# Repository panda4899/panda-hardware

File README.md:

Panda-Hardware
======

Devices, layouts, schematics, and parts for Team PANDA. 

Some custom parts we made that you may find useful:
* Wurth Electronics Inc 7447462330 Inductor
* ADS1115 Breakout Board
* CAT24C32 32-Kb I2C CMOS Serial EEPROM
* EM7180SFP
* HTU21D Breakout Board
* TSL2561 Breakout Board
* MC74VHC1GT125 Noninverting Buffer / CMOS Logic Level Shifter
* Mini-360 DC/DC
* P82B715 I2C Bus Extender
* Recom R-78E5.0-1.0 switching regulator
* MQ series sensor socket

All of these should work but please check them before you make a board.

MCP23008 from [Adafruit](https://github.com/adafruit/Adafruit-Eagle-Library)

Raspberry Pi B+ GPIO Header 2x20 pin, TSSOP-5, SOT23-5, RJ45-8, LM358, M02, M03, M04, M05, M06, M07, M09, M10, and M12 from [Sparkfun](https://github.com/sparkfun/SparkFun-Eagle-Libraries)

Released under the [Creative Commons ShareAlike 4.0 International](https://creativecommons.org/licenses/by-sa/4.0/) license.

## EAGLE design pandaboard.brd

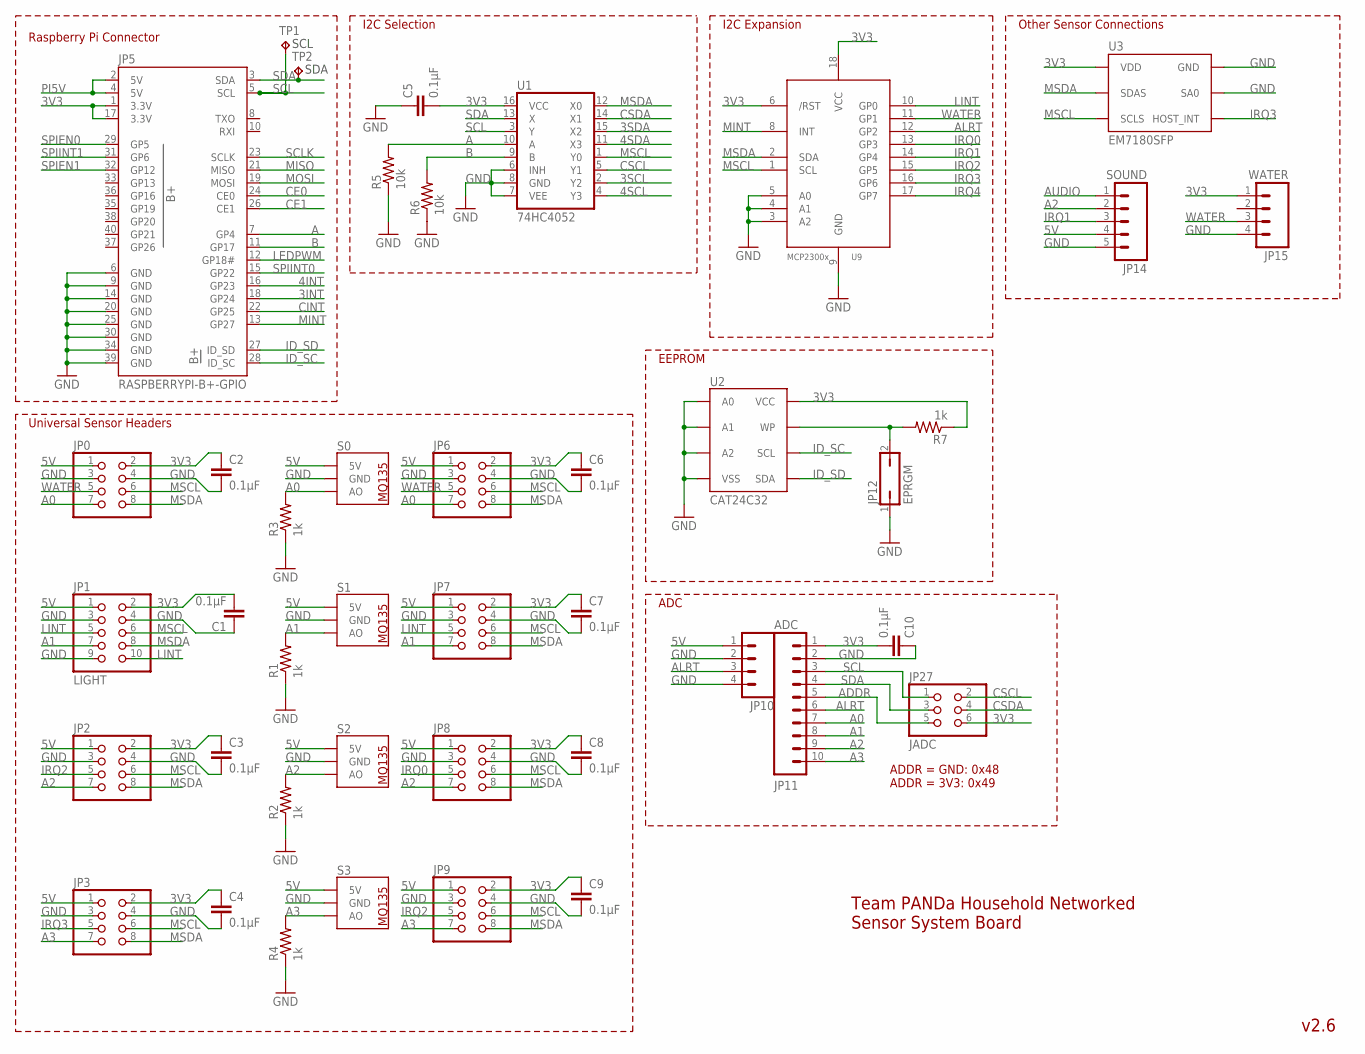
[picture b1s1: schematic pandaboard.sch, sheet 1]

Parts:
C1, C2, C3, C4, C5, C6, C7, C8, C9, C10: 0.1µF; C1206
JP0, JP2, JP3, JP6, JP7, JP8, JP9: PINHD-2X4; 2X04
JP1: LIGHT; 2X05
JP5: RASPBERRYPI-B+-GPIO; 2X20-SHROUDED
JP10: M04PTH; 1X04
JP11: ADC; 1X10
JP12: EPRGM; JP1
JP14: SOUND; 1X05_LOCK
JP15: WATER; 1X04_LOCK
JP27: JADC; 2X03
R1, R2, R3, R4, R7: 1k; R1206
R5, R6: 10k; R1206
S0, S1, S2, S3: VOC
TP1, TP2: TPPAD1-13; P1-13
U1: 74HC4052; DIL16
U2: CAT24C32; DIL08
U3: EM7180SFP
U9: MCP23008/P; DIL18

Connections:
3INT: JP5.18 (GP24); also elsewhere on the board
3SCL: U1.2 (Y2); also elsewhere on the board
3SDA: U1.15 (X2); also elsewhere on the board
3V3: C1.2, C2.1, C3.1, C4.1, C5.2, C6.1, C7.1, C8.1, C9.1, C10.2, JP0.2, JP1.2, JP2.2, JP3.2, JP5.1 (3.3V), JP5.17 (3.3V), JP6.2, JP7.2, JP8.2, JP9.2, JP11.1, JP15.1, JP27.6, R7.1, U1.16 (VCC), U2.8 (VCC), U3.VDD, U9.6 (/RST), U9.18 (VCC); also elsewhere on the board
4INT: JP5.16 (GP23); also elsewhere on the board
4SCL: U1.4 (Y3); also elsewhere on the board
4SDA: U1.11 (X3); also elsewhere on the board
5V: JP0.1, JP1.1, JP2.1, JP3.1, JP6.1, JP7.1, JP8.1, JP9.1, JP10.1, JP14.4, S0.A (5V), S0.A@2 (5V), S0.H (5V), S1.A (5V), S1.A@2 (5V), S1.H (5V), S2.A (5V), S2.A@2 (5V), S2.H (5V), S3.A (5V), S3.A@2 (5V), S3.H (5V); also elsewhere on the board
A: JP5.7 (GP4), R5.2, U1.10 (A)
A0: JP0.7, JP6.7, JP11.7, R3.2, S0.B (AO), S0.B@2 (AO)
A1: JP1.7, JP7.7, JP11.8, R1.2, S1.B (AO), S1.B@2 (AO)
A2: JP2.7, JP8.7, JP11.9, JP14.2, R2.2, S2.B (AO), S2.B@2 (AO)
A3: JP3.7, JP9.7, JP11.10, R4.2, S3.B (AO), S3.B@2 (AO)
ADDR: JP11.5, JP27.5
ALRT: JP10.3, JP11.6, U9.12 (GP2)
AUDIO: JP14.1
B: JP5.11 (GP17), R6.2, U1.9 (B)
CE0: JP5.24 (CE0); also elsewhere on the board
CE1: JP5.26 (CE1); also elsewhere on the board
CINT: JP5.22 (GP25); also elsewhere on the board
CSCL: JP27.2, U1.5 (Y1); also elsewhere on the board
CSDA: JP27.4, U1.14 (X1); also elsewhere on the board
GND: C1.1, C2.2, C3.2, C4.2, C5.1, C6.2, C7.2, C8.2, C9.2, C10.1, JP0.3, JP0.4, JP1.3, JP1.4, JP1.9, JP2.3, JP2.4, JP3.3, JP3.4, JP5.6 (GND), JP5.9 (GND), JP5.14 (GND), JP5.20 (GND), JP5.25 (GND), JP5.30 (GND), JP5.34 (GND), JP5.39 (GND), JP6.3, JP6.4, JP7.3, JP7.4, JP8.3, JP8.4, JP9.3, JP9.4, JP10.2, JP10.4, JP11.2, JP12.1, JP14.5, JP15.4, R1.1, R2.1, R3.1, R4.1, R5.1, R6.1, S0.H@2 (GND), S1.H@2 (GND), S2.H@2 (GND), S3.H@2 (GND), U1.6 (INH), U1.7 (VEE), U1.8 (GND), U2.1 (A0), U2.2 (A1), U2.3 (A2), U2.4 (VSS), U3.GND, U3.SA0, U9.3 (A2), U9.4 (A1), U9.5 (A0), U9.9 (GND); also elsewhere on the board
ID_SC: JP5.28 (ID_SC), U2.6 (SCL)
ID_SD: JP5.27 (ID_SD), U2.5 (SDA)
IRQ0: JP8.5, U9.13 (GP3)
IRQ1: JP14.3, U9.14 (GP4)
IRQ2: JP2.5, JP9.5, U9.15 (GP5)
IRQ3: JP3.5, U3.HOST_INT, U9.16 (GP6)
IRQ4: U9.17 (GP7)
LEDPWM: JP5.12 (GP18#); also elsewhere on the board
LINT: JP1.5, JP1.10, JP7.5, U9.10 (GP0)
MINT: JP5.13 (GP27), U9.8 (INT); also elsewhere on the board
MISO: JP5.21 (MISO); also elsewhere on the board
MOSI: JP5.19 (MOSI); also elsewhere on the board
MSCL: JP0.6, JP1.6, JP2.6, JP3.6, JP6.6, JP7.6, JP8.6, JP9.6, U1.1 (Y0), U3.SCLS, U9.1 (SCL); also elsewhere on the board
MSDA: JP0.8, JP1.8, JP2.8, JP3.8, JP6.8, JP7.8, JP8.8, JP9.8, U1.12 (X0), U3.SDAS, U9.2 (SDA); also elsewhere on the board
unnamed: JP12.2, R7.2, U2.7 (WP)
PI5V: JP5.2 (5V), JP5.4 (5V); also elsewhere on the board
SCL: JP5.5 (SCL), JP11.3, JP27.1, TP1.TP, U1.3 (Y)
SCLK: JP5.23 (SCLK); also elsewhere on the board
SDA: JP5.3 (SDA), JP11.4, JP27.3, TP2.TP, U1.13 (X)
SPIEN0: JP5.29 (GP5); also elsewhere on the board
SPIEN1: JP5.32 (GP12); also elsewhere on the board
SPIINT0: JP5.15 (GP22); also elsewhere on the board
SPIINT1: JP5.31 (GP6); also elsewhere on the board
WATER: JP0.5, JP6.5, JP15.3, U9.11 (GP1)

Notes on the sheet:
v2.6
I2C Selection
Raspberry Pi Connector
Universal Sensor Headers
Other Sensor Connections
I2C Expansion
EEPROM
Team PANDa Household Networked Sensor System Board
ADDR = GND: 0x48 ADDR = 3V3: 0x49
ADC

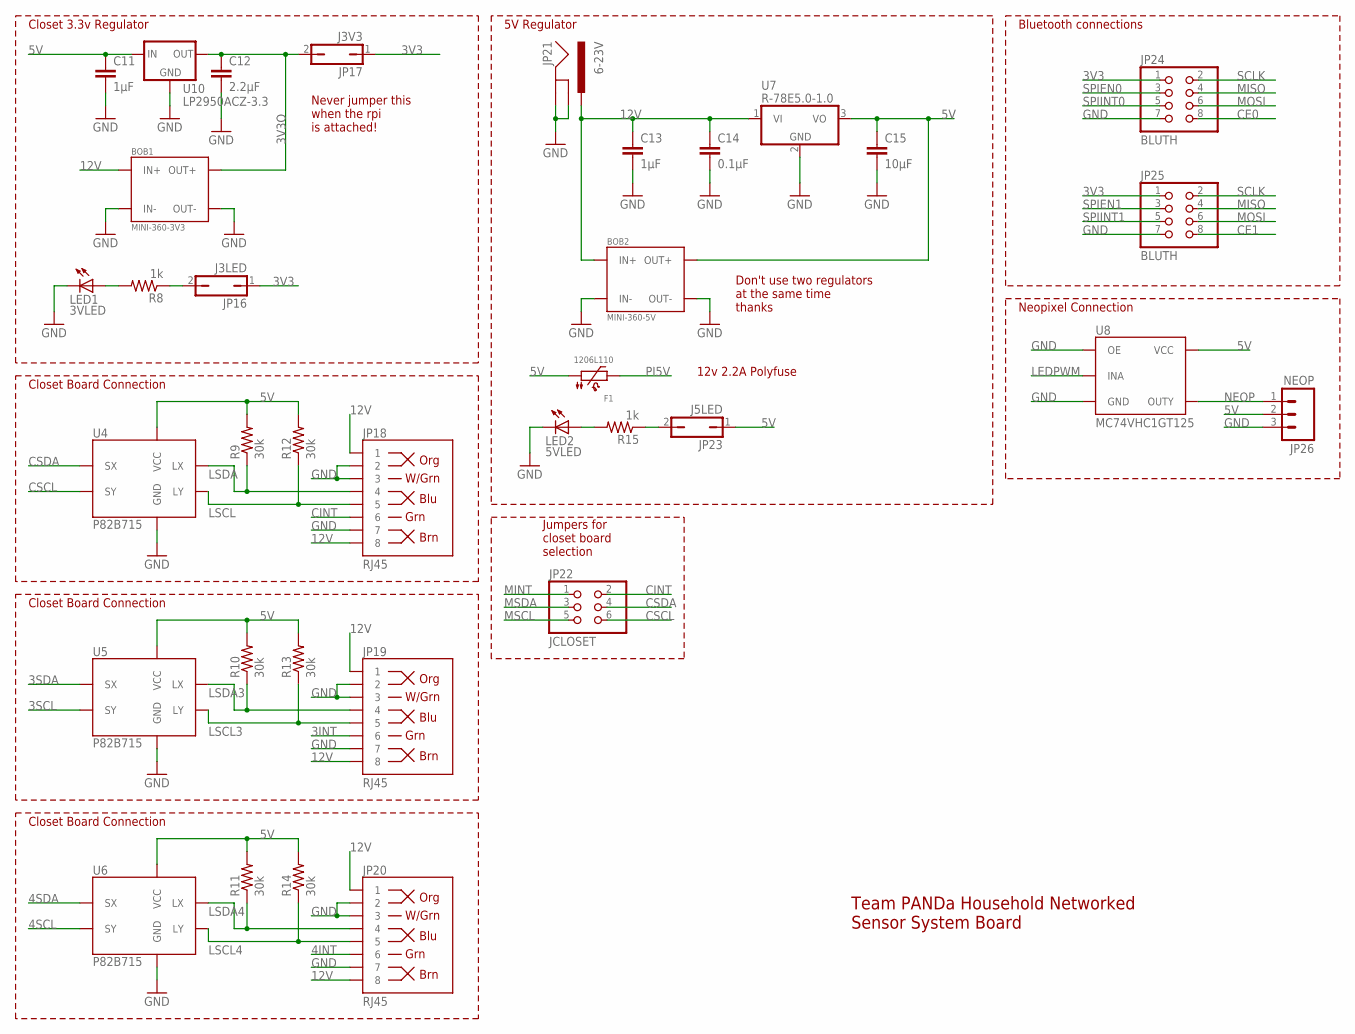
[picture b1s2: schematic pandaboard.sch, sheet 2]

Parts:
BOB1: MINI-360-3V3; MINI-360
BOB2: MINI-360-5V; MINI-360
C11, C13: 1µF; C1206
C12: 2.2µF; C1206
C14: 0.1µF; C1206
C15: 10µF; C1206
F1: 1206L110; 1206
JP16: J3LED; JP1
JP17: J3V3; JP1
JP18, JP19, JP20: RJ45; RJ45-8
JP21: 6-23V; POWER_JACK_PTH_BREAD
JP22: JCLOSET; 2X03
JP23: J5LED; JP1
JP24, JP25: BLUTH; 2X04
JP26: NEOP; 1X03
LED1: 3VLED; LED_1206
LED2: 5VLED; LED_1206
R8, R15: 1k; R1206
R9, R10, R11, R12, R13, R14: 30k; R1206
U4, U5, U6: P82B715; DIL08
U7: R-78E5.0-1.0; R-78E
U8: MC74VHC1GT125; SOT23-5
U10: LP2950ACZ-3.3; TO92

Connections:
3INT: JP19.6; also elsewhere on the board
3SCL: U5.6 (SY); also elsewhere on the board
3SDA: U5.3 (SX); also elsewhere on the board
3V3: JP16.1, JP17.1, JP24.1, JP25.1; also elsewhere on the board
3V3O: BOB1.OUT+, C12.1, JP17.2, U10.1 (OUT)
4INT: JP20.6; also elsewhere on the board
4SCL: U6.6 (SY); also elsewhere on the board
4SDA: U6.3 (SX); also elsewhere on the board
5V: BOB2.OUT+, C11.1, C15.1, F1.1, JP23.1, JP26.2, R9.2, R10.2, R11.2, R12.2, R13.2, R14.2, U4.8 (VCC), U5.8 (VCC), U6.8 (VCC), U7.3 (VO), U8.5 (VCC), U10.3 (IN); also elsewhere on the board
12V: BOB1.IN+, BOB2.IN+, C13.1, C14.1, JP18.1, JP18.8, JP19.1, JP19.8, JP20.1, JP20.8, JP21.PWR, U7.1 (VI)
CE0: JP24.8; also elsewhere on the board
CE1: JP25.8; also elsewhere on the board
CINT: JP18.6, JP22.2; also elsewhere on the board
CSCL: JP22.6, U4.6 (SY); also elsewhere on the board
CSDA: JP22.4, U4.3 (SX); also elsewhere on the board
GND: BOB1.IN-, BOB1.OUT-, BOB2.IN-, BOB2.OUT-, C11.2, C12.2, C13.2, C14.2, C15.2, JP18.2, JP18.3, JP18.7, JP19.2, JP19.3, JP19.7, JP20.2, JP20.3, JP20.7, JP21.GND, JP21.GNDBREAK, JP24.7, JP25.7, JP26.3, LED1.C, LED2.C, U4.4 (GND), U5.4 (GND), U6.4 (GND), U7.2 (GND), U8.1 (OE), U8.3 (GND), U10.2 (GND); also elsewhere on the board
LEDPWM: U8.2 (INA); also elsewhere on the board
LSCL: JP18.5, R12.1, U4.7 (LY)
LSCL3: JP19.5, R13.1, U5.7 (LY)
LSCL4: JP20.5, R14.1, U6.7 (LY)
LSDA: JP18.4, R9.1, U4.2 (LX)
LSDA3: JP19.4, R10.1, U5.2 (LX)
LSDA4: JP20.4, R11.1, U6.2 (LX)
MINT: JP22.1; also elsewhere on the board
MISO: JP24.4, JP25.4; also elsewhere on the board
MOSI: JP24.6, JP25.6; also elsewhere on the board
MSCL: JP22.5; also elsewhere on the board
MSDA: JP22.3; also elsewhere on the board
unnamed: JP23.2, R15.1
unnamed: LED2.A, R15.2
unnamed: LED1.A, R8.2
unnamed: JP16.2, R8.1
NEOP: JP26.1, U8.4 (OUTY)
PI5V: F1.2; also elsewhere on the board
SCLK: JP24.2, JP25.2; also elsewhere on the board
SPIEN0: JP24.3; also elsewhere on the board
SPIEN1: JP25.3; also elsewhere on the board
SPIINT0: JP24.5; also elsewhere on the board
SPIINT1: JP25.5; also elsewhere on the board

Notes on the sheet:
5V Regulator
Closet 3.3v Regulator
Don't use two regulators at the same time thanks
Closet Board Connection
Jumpers for closet board selection
Never jumper this when the rpi is attached!
Bluetooth connections
Neopixel Connection
Team PANDa Household Networked Sensor System Board
12v 2.2A Polyfuse

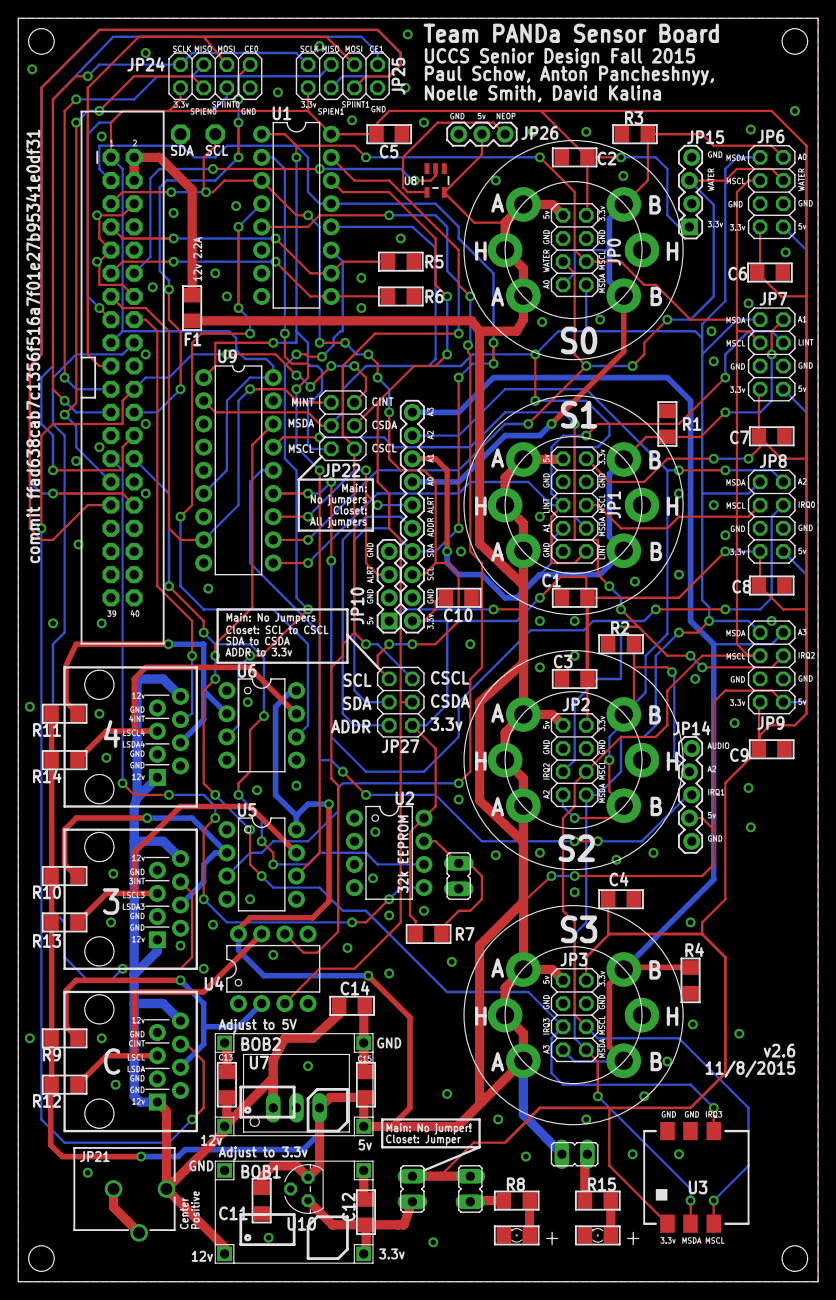
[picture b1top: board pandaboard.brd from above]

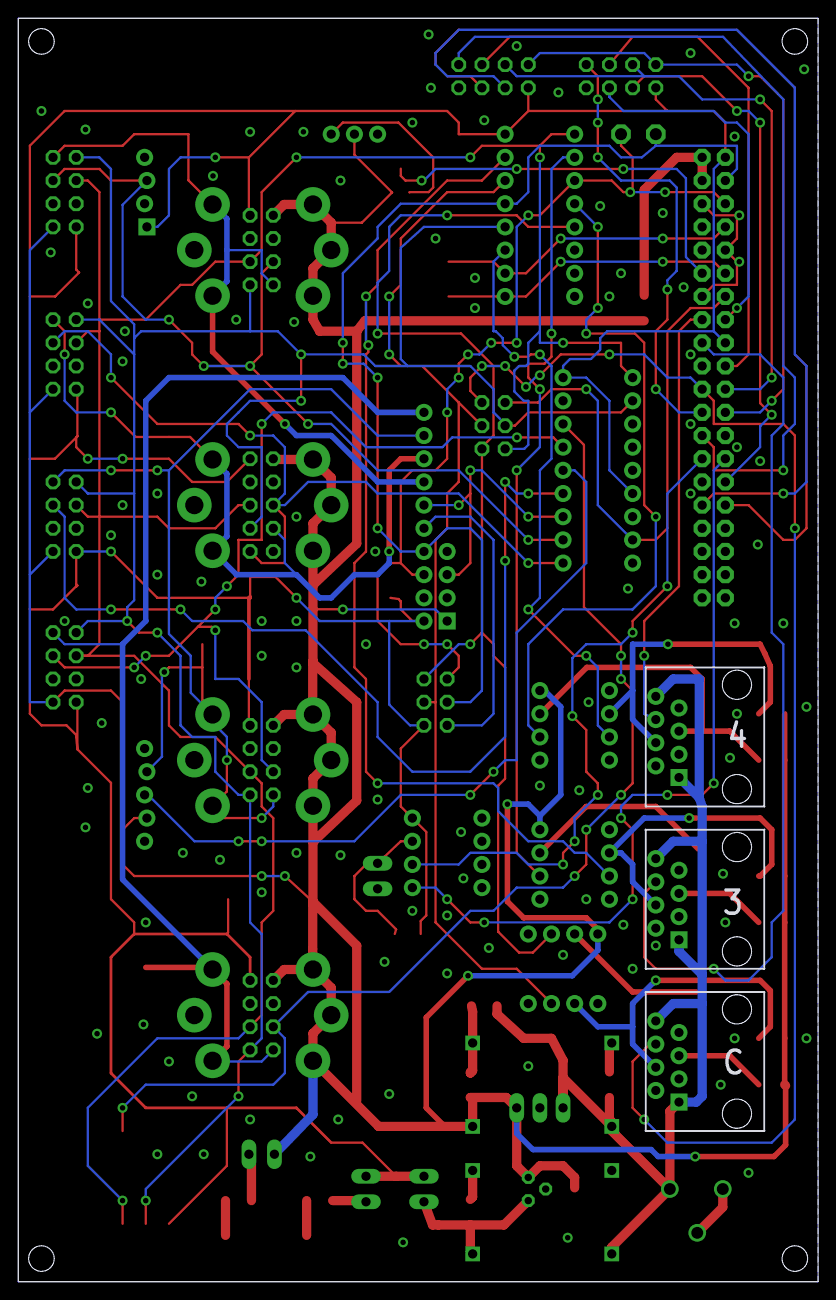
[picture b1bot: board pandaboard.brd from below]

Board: 2 copper layers, 87.6 x 138.4 mm, 78 parts (3 on the bottom side), 58 nets.

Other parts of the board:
U$1: PUPPY

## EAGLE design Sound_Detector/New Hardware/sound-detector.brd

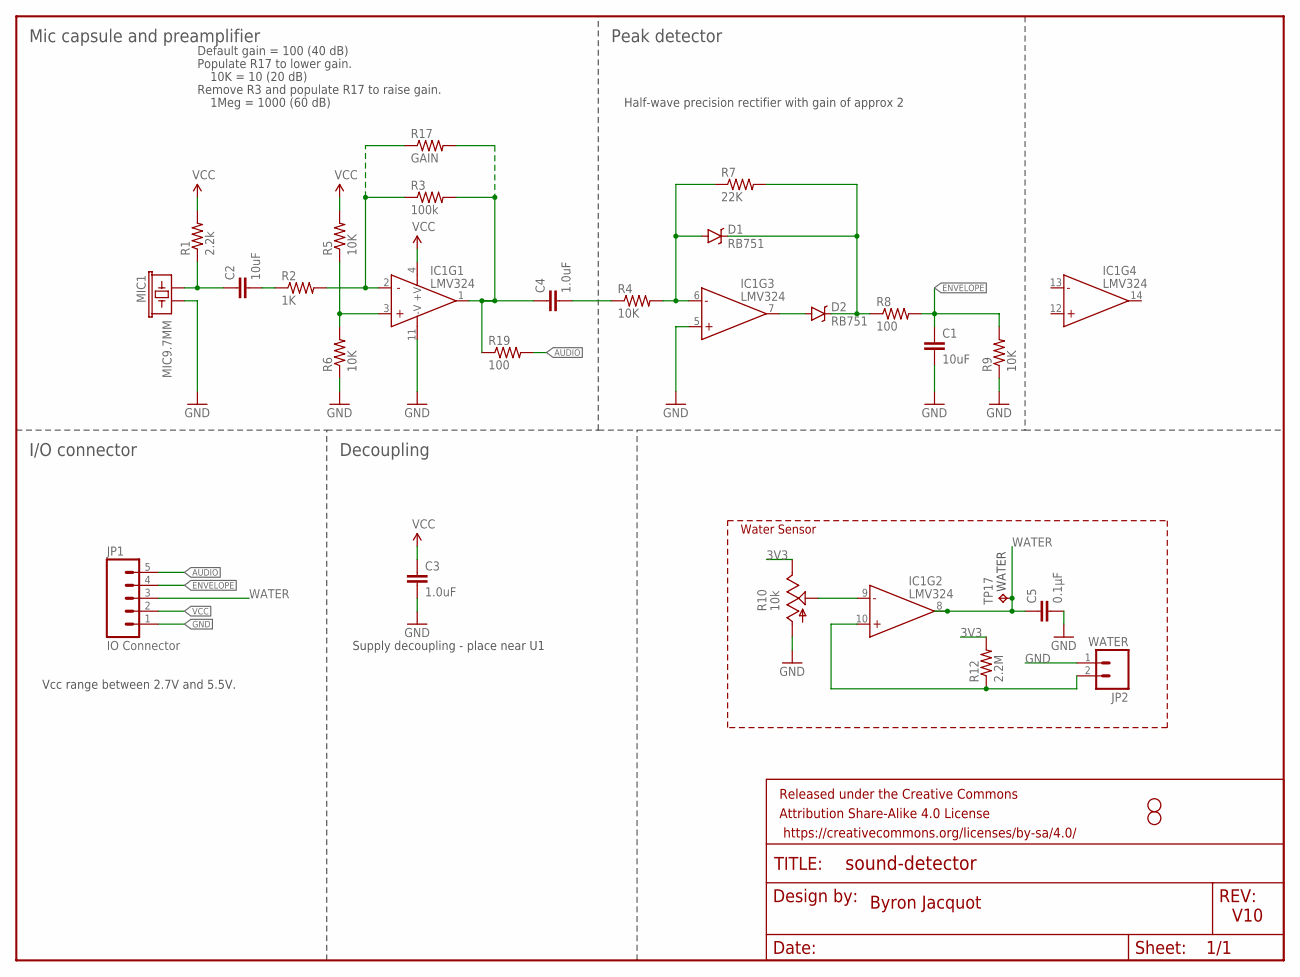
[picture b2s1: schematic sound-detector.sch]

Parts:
C1, C2: 10uF; 1206
C3, C4: 1.0uF; 0603-CAP
C5: 0.1µF; C1206
D1, D2: RB751; SOD-523
FRAME1: FRAME-LETTER; CREATIVE_COMMONS
IC1: LMV324; SO014
JP1: IO Connector; 1X05
JP2: WATER; SCREWTERMINAL-3.5MM-2
MIC1: MIC9.7MM; MIC-9.7MM
R1: 2.2k; 0603-RES@1
R2: 1K; 0603-RES@1
R3: 100k; 0603-RES@1
R4, R5, R6, R9: 10K; 0603-RES@1
R7: 22K; 0603-RES
R8, R19: 100; 0603-RES@1
R10: 10k; B64Y
R12: 2.2M; R1206
R17: GAIN; AXIAL-0.1EZ
STANDOFF1, STANDOFF2: STAND-OFF
TP17: TPPAD1-13; P1-13

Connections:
3V3: R10.E, R12.2
AUDIO: JP1.5, R19.2
ENVELOPE: JP1.4
GND: C1.2, C3.2, C5.2, IC1.5 (+IN), IC1.11 (-V), JP1.1, JP2.1, MIC1.2, R6.1, R9.1, R10.A
N$: C4.1, IC1.1 (OUT), R3.2, R17.P$2 (2), R19.1
unnamed: C2.1, MIC1.1, R1.1
unnamed: IC1.3 (+IN), R5.1, R6.2
unnamed: IC1.2 (-IN), R2.2, R3.1, R17.P$1 (1)
unnamed: C2.2, R2.1
unnamed: C4.2, R4.1
unnamed: D1.A, IC1.6 (-IN), R4.2, R7.1
unnamed: D2.A, IC1.7 (OUT)
unnamed: D1.C, D2.C, R7.2, R8.1
unnamed: C1.1, R8.2, R9.2
unnamed: IC1.9 (-IN), R10.S
unnamed: IC1.10 (+IN), JP2.2, R12.1
VCC: C3.1, IC1.4 (+V), JP1.2, R1.2, R5.2
WATER: C5.1, IC1.8 (OUT), JP1.3, TP17.TP

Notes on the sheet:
Byron Jacquot
V10
Supply decoupling - place near U1
Mic capsule and preamplifier
Peak detector
I/O connector
Decoupling
Default gain = 100 (40 dB)
Half-wave precision rectifier with gain of approx 2
Vcc range between 2.7V and 5.5V.
Populate R17 to lower gain.
10K = 10 (20 dB)
Remove R3 and populate R17 to raise gain.
1Meg = 1000 (60 dB)
Water Sensor

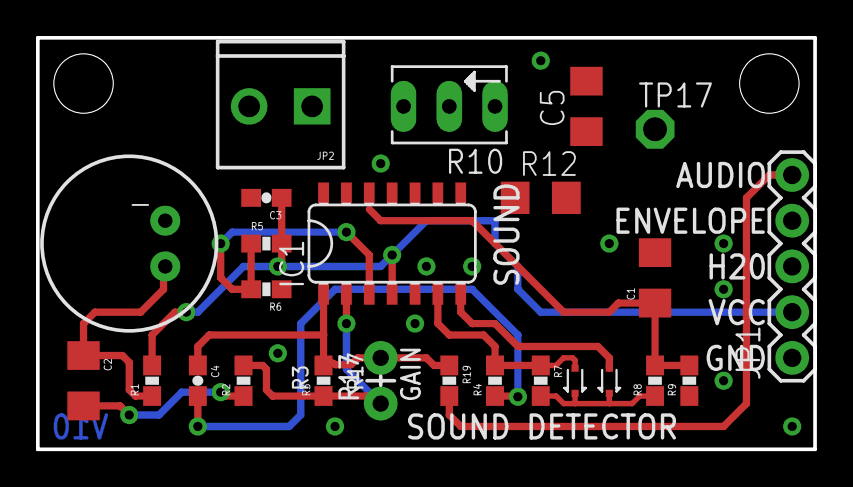
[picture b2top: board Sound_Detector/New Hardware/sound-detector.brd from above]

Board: 2 copper layers, 43.2 x 22.9 mm, 28 parts (0 on the bottom side), 17 nets.

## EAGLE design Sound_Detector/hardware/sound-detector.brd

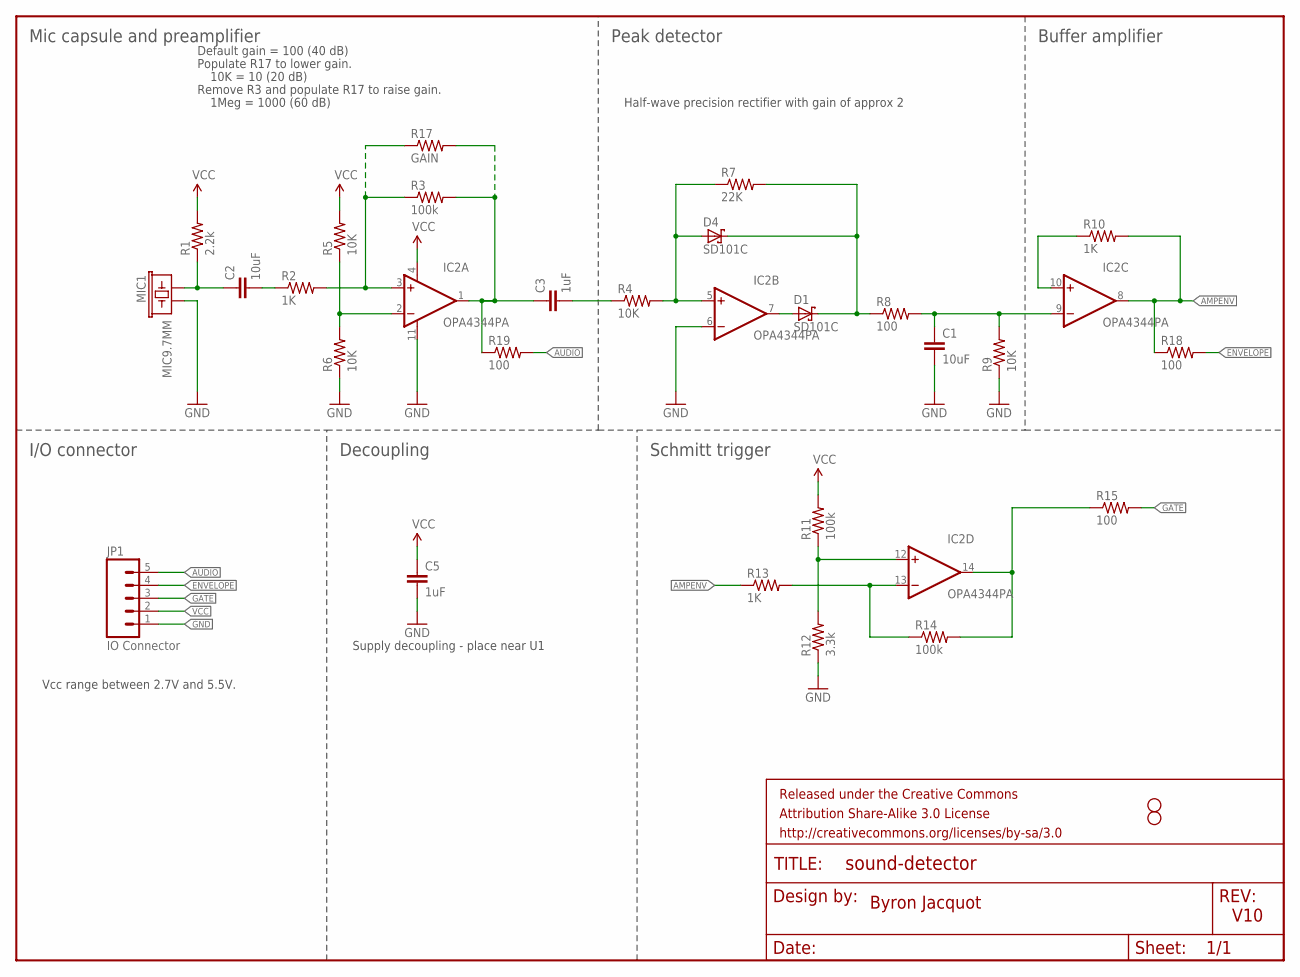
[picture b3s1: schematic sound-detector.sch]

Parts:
C1, C2: 10uF; 1206
C3, C5: 1uF; 1206
D1, D4: SD101C; DO35-7
FRAME1: FRAME-LETTER; CREATIVE_COMMONS
IC2: OPA4344PA; DIL14
JP1: IO Connector; 1X05
MIC1: MIC9.7MM; MIC-9.7MM
R1: 2.2k; R1206
R2, R10, R13: 1K; R1206
R3, R11, R14: 100k; R1206
R4, R5, R6, R9: 10K; R1206
R7: 22K; R1206
R8, R15, R18, R19: 100; R1206
R12: 3.3k; R1206
R17: GAIN; R1206
STANDOFF1, STANDOFF2: STAND-OFF

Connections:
AMPENV: IC2.8 (OUT), R10.2, R13.1, R18.1
AUDIO: JP1.5, R19.2
ENVELOPE: JP1.4, R18.2
GATE: JP1.3, R15.2
GND: C1.2, C5.2, IC2.6 (-IN), IC2.11 (V-), JP1.1, MIC1.2, R6.1, R9.1, R12.1
N$: C3.1, IC2.1 (OUT), R3.2, R17.2, R19.1
unnamed: C2.1, MIC1.1, R1.1
unnamed: IC2.2 (-IN), R5.1, R6.2
unnamed: IC2.3 (+IN), R2.2, R3.1, R17.1
unnamed: C2.2, R2.1
unnamed: C3.2, R4.1
unnamed: D4.A, IC2.5 (+IN), R4.2, R7.1
unnamed: D1.A, IC2.7 (OUT)
unnamed: D1.C, D4.C, R7.2, R8.1
unnamed: C1.1, IC2.9 (-IN), R8.2, R9.2
unnamed: IC2.10 (+IN), R10.1
unnamed: IC2.12 (+IN), R11.1, R12.2
unnamed: IC2.13 (-IN), R13.2, R14.1
unnamed: IC2.14 (OUT), R14.2, R15.1
VCC: C5.1, IC2.4 (V+), JP1.2, R1.2, R5.2, R11.2

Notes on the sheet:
Byron Jacquot
V10
Supply decoupling - place near U1
Mic capsule and preamplifier
Peak detector
Buffer amplifier
I/O connector
Decoupling
Schmitt trigger
Default gain = 100 (40 dB)
Half-wave precision rectifier with gain of approx 2
Vcc range between 2.7V and 5.5V.
Populate R17 to lower gain.
10K = 10 (20 dB)
Remove R3 and populate R17 to raise gain.
1Meg = 1000 (60 dB)

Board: 2 copper layers, 30 parts (0 on the bottom side), 20 nets, no tracks yet.

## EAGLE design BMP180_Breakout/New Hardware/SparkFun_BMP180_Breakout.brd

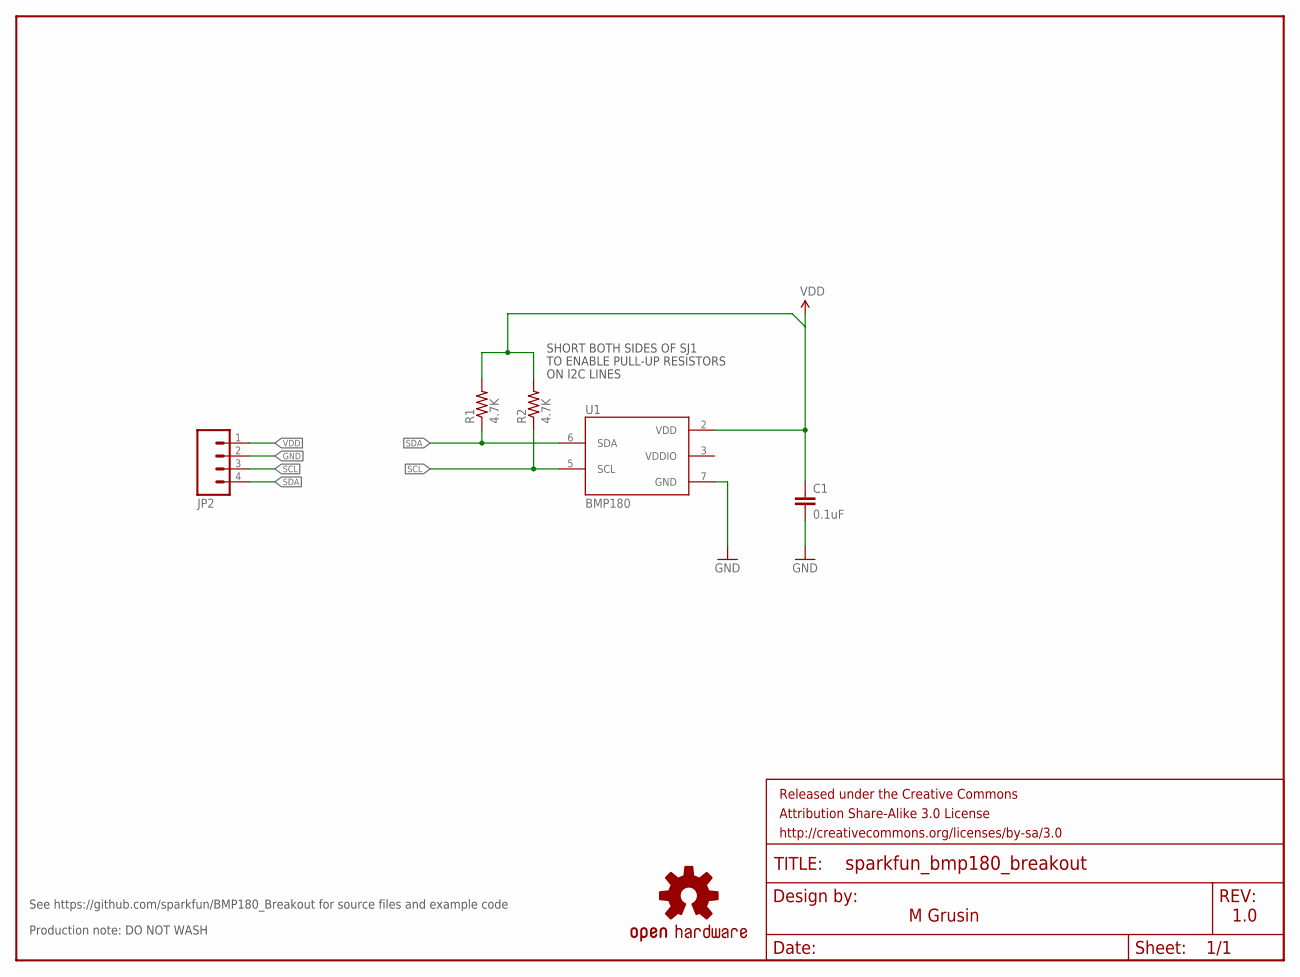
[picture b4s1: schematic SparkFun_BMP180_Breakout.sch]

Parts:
C1: 0.1uF; 0603-CAP
FRAME1: FRAME-LETTER; CREATIVE_COMMONS
JP2: M04PTH; 1X04
LOGO2: OSHW-LOGOS; OSHW-LOGO-S
R1, R2: 4.7K; 0603-RES
U1: BMP180

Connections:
GND: C1.2, JP2.2, U1.7 (GND)
SCL: JP2.3, R2.1, U1.5 (SCL)
SDA: JP2.4, R1.1, U1.6 (SDA)
VDD: C1.1, JP2.1, R1.2, R2.2, U1.2 (VDD)
VDDIO: U1.3 (VDDIO)

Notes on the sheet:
M Grusin
SHORT BOTH SIDES OF SJ1
TO ENABLE PULL-UP RESISTORS
ON I2C LINES
1.0
Production note: DO NOT WASH
See https://github.com/sparkfun/BMP180_Breakout for source files and example code

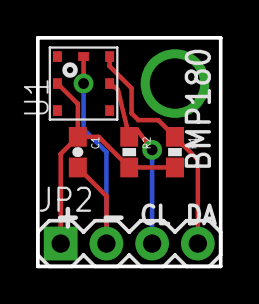
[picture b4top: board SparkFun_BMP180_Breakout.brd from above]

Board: 2 copper layers, 10.2 x 12.7 mm, 7 parts (1 on the bottom side), 4 nets.

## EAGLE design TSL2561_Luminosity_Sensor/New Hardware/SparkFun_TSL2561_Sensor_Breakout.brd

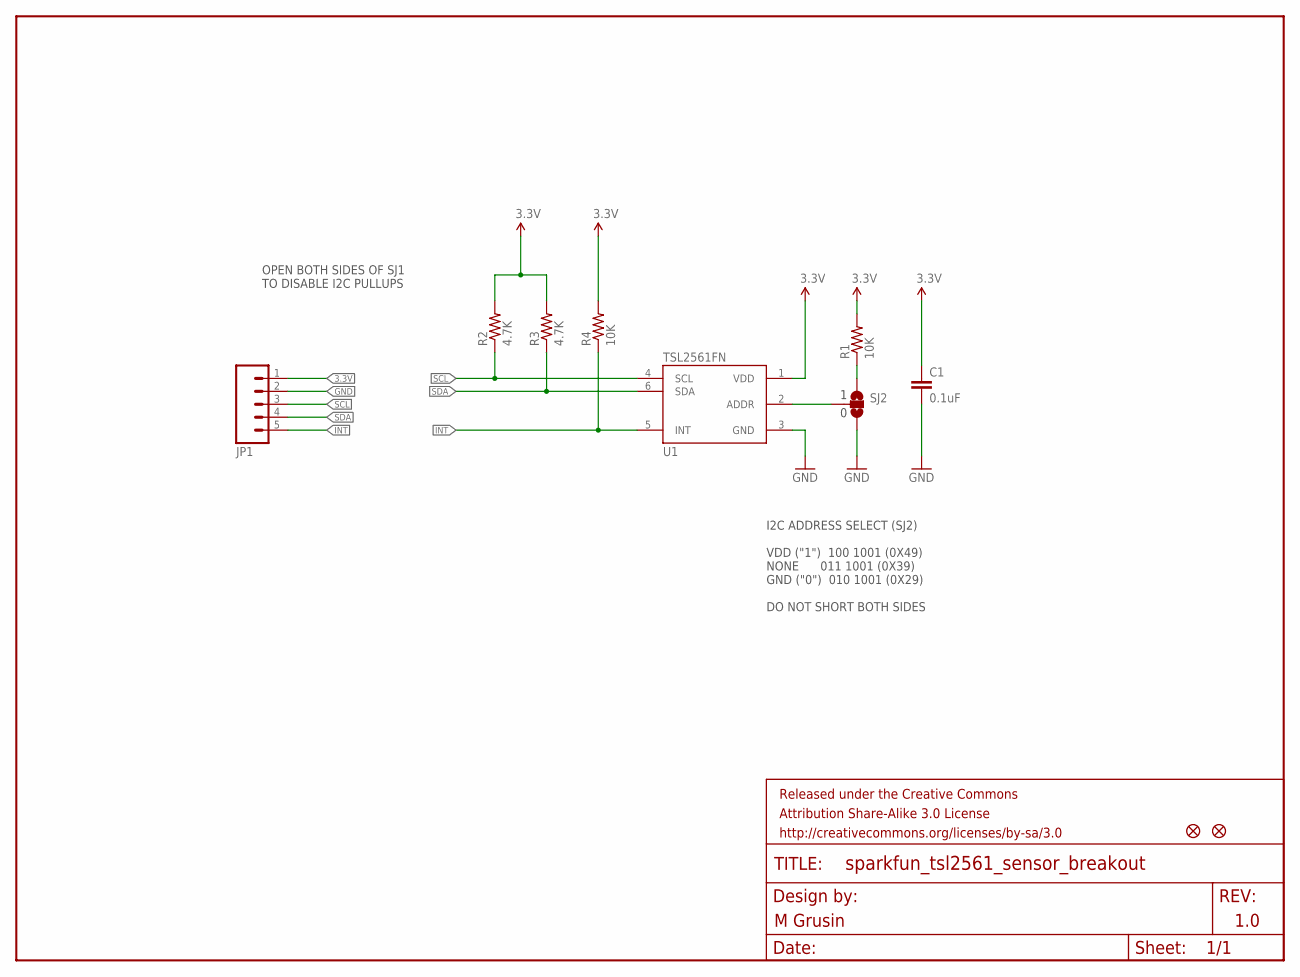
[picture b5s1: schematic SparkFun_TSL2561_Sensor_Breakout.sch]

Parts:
C1: 0.1uF; 0603-CAP
FID1, FID2: FIDUCIALUFIDUCIAL; MICRO-FIDUCIAL
FRAME1: FRAME-LETTER; CREATIVE_COMMONS
JP1: M05NO_SILK; 1X05_NO_SILK
R1, R4: 10K; 0603-RES
R2, R3: 4.7K; 0603-RES
SJ2: SOLDERJUMPER_2WAYS; SJ_3
U1: TSL2561FN; FN-6

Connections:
3.3V: C1.1, JP1.1, R1.2, R2.2, R3.2, R4.2, U1.1 (VDD)
GND: C1.2, JP1.2, SJ2.3, U1.3 (GND)
INT: JP1.5, R4.1, U1.5 (INT)
unnamed: R1.1, SJ2.1
unnamed: SJ2.2, U1.2 (ADDR)
SCL: JP1.3, R2.1, U1.4 (SCL)
SDA: JP1.4, R3.1, U1.6 (SDA)

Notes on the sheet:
I2C ADDRESS SELECT (SJ2) VDD ("1") 100 1001 (0X49) NONE 011 1001 (0X39) GND ("0") 010 1001 (0X29) DO NOT SHORT BOTH SIDES
M Grusin
OPEN BOTH SIDES OF SJ1 TO DISABLE I2C PULLUPS
1.0

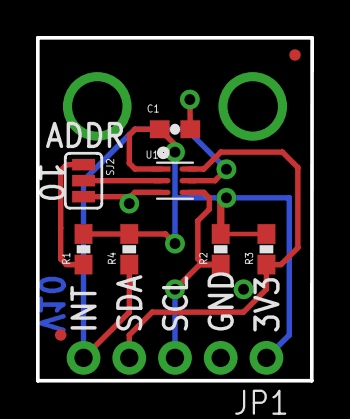
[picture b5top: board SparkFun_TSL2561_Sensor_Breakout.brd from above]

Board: 2 copper layers, 15.2 x 19.1 mm, 11 parts (0 on the bottom side), 7 nets.

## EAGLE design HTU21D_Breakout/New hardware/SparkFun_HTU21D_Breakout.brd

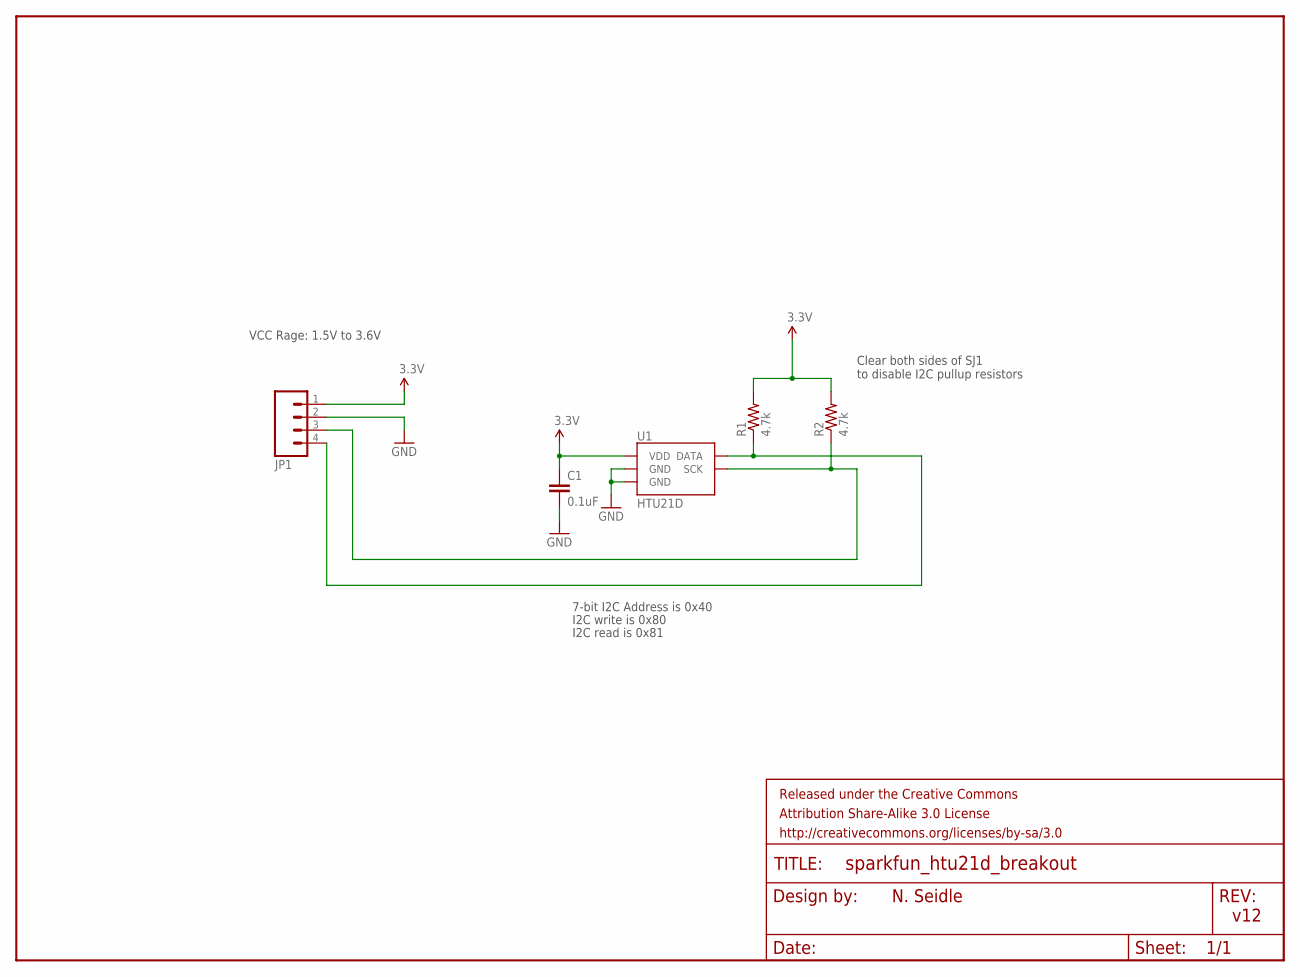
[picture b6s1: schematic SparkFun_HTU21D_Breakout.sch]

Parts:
C1: 0.1uF; 0603-CAP
FRAME2: FRAME-LETTER; CREATIVE_COMMONS
JP1: M04PTH; 1X04
R1, R2: 4.7k; 0603-RES
U1: HTU21D

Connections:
3.3V: C1.1, JP1.1, R1.2, R2.2, U1.VDD
GND: C1.2, JP1.2, U1.7 (GND), U1.GND
SCL: JP1.3, R2.1, U1.SCK
SDA: JP1.4, R1.1, U1.DATA

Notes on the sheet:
N. Seidle
Clear both sides of SJ1 to disable I2C pullup resistors
VCC Rage: 1.5V to 3.6V
7-bit I2C Address is 0x40
I2C write is 0x80
I2C read is 0x81
v12

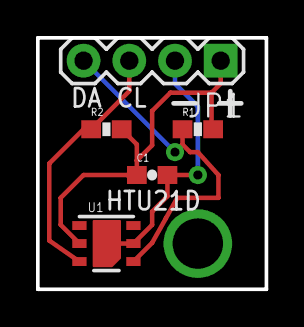
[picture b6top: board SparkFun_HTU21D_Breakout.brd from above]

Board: 2 copper layers, 12.7 x 14.0 mm, 6 parts (0 on the bottom side), 4 nets.

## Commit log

2015-09-18 Updated TSL2561 Breakout Board
2015-09-18 Added TSL2561 Breakout Board package, symbol, and device to library
2015-09-18 Minor style changes
2015-09-18 Added updated BMP180 Breakout Board
2015-09-18 Added BMP180 breakout to library
2015-09-18 Added MQ135 socket footprint
2015-09-20 Added 74HC4052
2015-09-20 Added P82B715
2015-09-20 Copied RPi GPIO connector, added readme
2015-09-20 Added LM2675
2015-09-20 Added Wurth Electronics Inc 7447462330
2015-09-20 Added USB Female A Connector
2015-09-21 Updated schematic
2015-09-22 Changed mounting hole location on HTU21D, TSL2561, and MQ135
2015-09-22 Added bypass capacitors
2015-09-22 Moved mounting holes for TSL2561
2015-09-24 Moved mounting holes on breakout boards
2015-09-25 Added R-78E5.0-1.0
2015-09-25 Copied RJ45 connector
2015-09-25 Changed 5V regulator, updated RJ45 jack
2015-09-25 Changed all capacitors to ceramic
2015-09-26 Added LM358
2015-09-26 Added water sensor
2015-09-27 Removed level conversion
2015-09-27 Forgot a power connection
2015-09-27 Added microphone
2015-09-27 Added audio section
2015-09-29 Adding headers to library
2015-09-29 Changed resistors and capacitors to smd, added test points, added extra connectors
2015-09-29 Fixed floating ADDR pin
2015-09-29 Aesthetics
2015-09-29 Renumbered
2015-09-30 Fixed incorrect layers
2015-10-04 Adding sound detector breakout
2015-10-04 Started modifying sound detector board for through-hole and 1206 components
2015-10-07 Moved water & audio to seperate schematic
2015-10-07 Start board layout
2015-10-08 Added M06
2015-10-08 Added M09
2015-10-08 More PCB work
2015-10-08 Back to original hardware
2015-10-08 Added M02
2015-10-08 Hybrid sound & water detector
2015-10-09 Adding more connectors
2015-10-09 Changed a few pad sizes
2015-10-09 Added locking style headers to BMP180, HTU21, and TSL2561
2015-10-09 Changed DIP package to round pads
2015-10-09 Fixed pressure sensor
2015-10-09 Fixed ADC silkscreen
2015-10-09 Changed PB82715 to round holes
2015-10-09 Updated footprints
2015-10-16 Changed label position
2015-10-16 Added CAT24C32
2015-10-16 Big change
2015-10-17 Added fuse and diode
2015-10-17 Added EM7180
2015-10-17 Visual change
2015-10-17 Copied TSSOP-5 footprint
2015-10-17 Copied SOT23-5 footprint
2015-10-17 Added MC74VHC1GT125
2015-10-17 Added Neopixel and bluetooth connectors
2015-10-17 Added Mini-360 DC/DC
2015-10-17 Added Mini-360 regulators
2015-10-17 Importing Lindsay changes
2015-10-17 Changed a few things
2015-10-17 Removed extra files
2015-10-18 Simplified jumpers
2015-10-18 Organized board and removed redundant test points
2015-10-18 Copied MCP32008
2015-10-18 Updated MCP32008 package
2015-10-19 Changed ADC configuration
2015-10-19 PCB layout changes
2015-10-20 Fixed EM7180SFP footprint
2015-10-20 Fixed R-78E footprint
2015-10-20 Fixed a few DIP footprints
2015-10-20 Fixed VOC footprint
2015-10-20 Fixed board dimensions
2015-10-22 Changed Layout
2015-10-22 Changed analog pins to match board
2015-10-22 Moved interrupts
2015-10-22 A lot of routing
2015-10-22 Almost done routing
2015-10-22 Routing complete
2015-10-22 Changed interrupts again
2015-10-22 Fully routed!
2015-10-22 Removed extra test points, changed solder mask relief
2015-10-23 Silkscreen improvements
2015-10-23 Changed silkscreen text sizes
2015-10-23 Added vias
2015-10-23 Silkscreen revisions
2015-10-23 Removed testpoints, added vias
2015-10-25 Changed design rules, moved a few vias
2015-10-25 Added more vias
2015-10-25 Renamed 2 parts, moved a few traces
2015-10-26 Aesthetic changes, updated version
2015-10-26 Moved a few components
2015-10-26 Finishing touches
2015-10-26 Gerbers for first production run!
2015-10-30 Fixed R-78 footprint
2015-10-31 Updated gerbers
2015-11-05 Fixed silkscreen error
2015-11-06 Removed diode
2015-11-06 Simplified ADC jumpers
2015-11-07 Removed old gerbers
2015-11-07 Moved water and sound connectors
2015-11-07 Updated fuse footprint
2015-11-07 Added locking connectors
2015-11-07 Switched ADC connector back to normal
2015-11-07 Changed expanders to use 5V
2015-11-08 Updated silkscreen
2015-11-08 Moved connectors
2015-11-08 Minor tweaks
2015-11-09 Added gerbers
2015-11-30 Changed pullup resistor value
2015-12-11 Added Datasheets
2015-12-11 Added Users Guide

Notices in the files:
parts and their libraries:
SparkFun-Aesthetics: Licensing: CC v3.0 Share-Alike You are welcome to use this library for commercial purposes.
SparkFun-Aesthetics: Released under the Creative Commons Attribution Share-Alike 3.0 License
SparkFun-Aesthetics: http://creativecommons.org/licenses/by-sa/3.0
